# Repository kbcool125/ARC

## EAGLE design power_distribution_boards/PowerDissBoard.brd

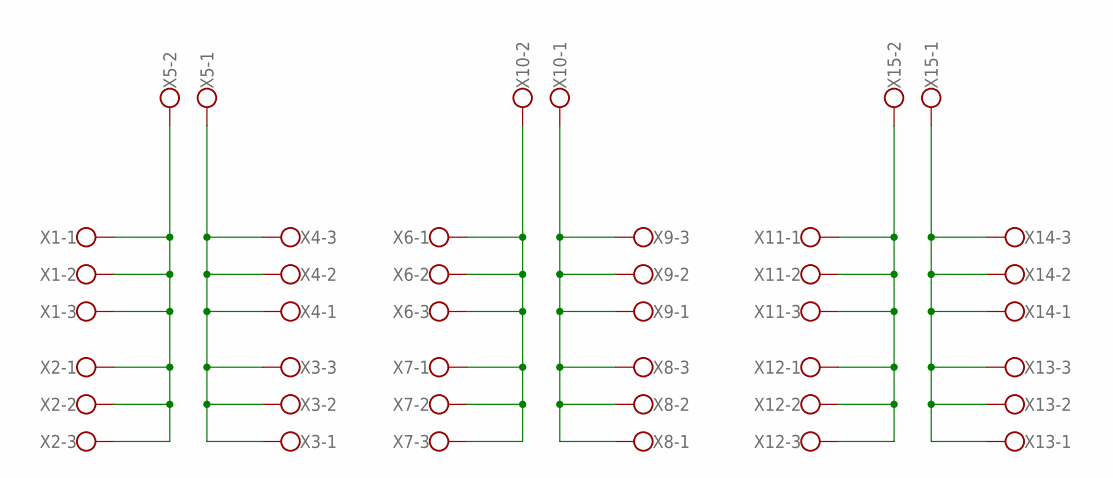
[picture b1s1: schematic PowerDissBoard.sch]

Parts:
X1, X2, X3, X4, X6, X7, X8, X9, X11, X12, X13, X14: W237-103
X5, X10, X15: W237-102

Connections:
unnamed: X1.1, X1.2, X1.3, X2.1, X2.2, X2.3, X5.2
unnamed: X3.1, X3.2, X3.3, X4.1, X4.2, X4.3, X5.1
unnamed: X6.1, X6.2, X6.3, X7.1, X7.2, X7.3, X10.2
unnamed: X8.1, X8.2, X8.3, X9.1, X9.2, X9.3, X10.1
unnamed: X11.1, X11.2, X11.3, X12.1, X12.2, X12.3, X15.2
unnamed: X13.1, X13.2, X13.3, X14.1, X14.2, X14.3, X15.1

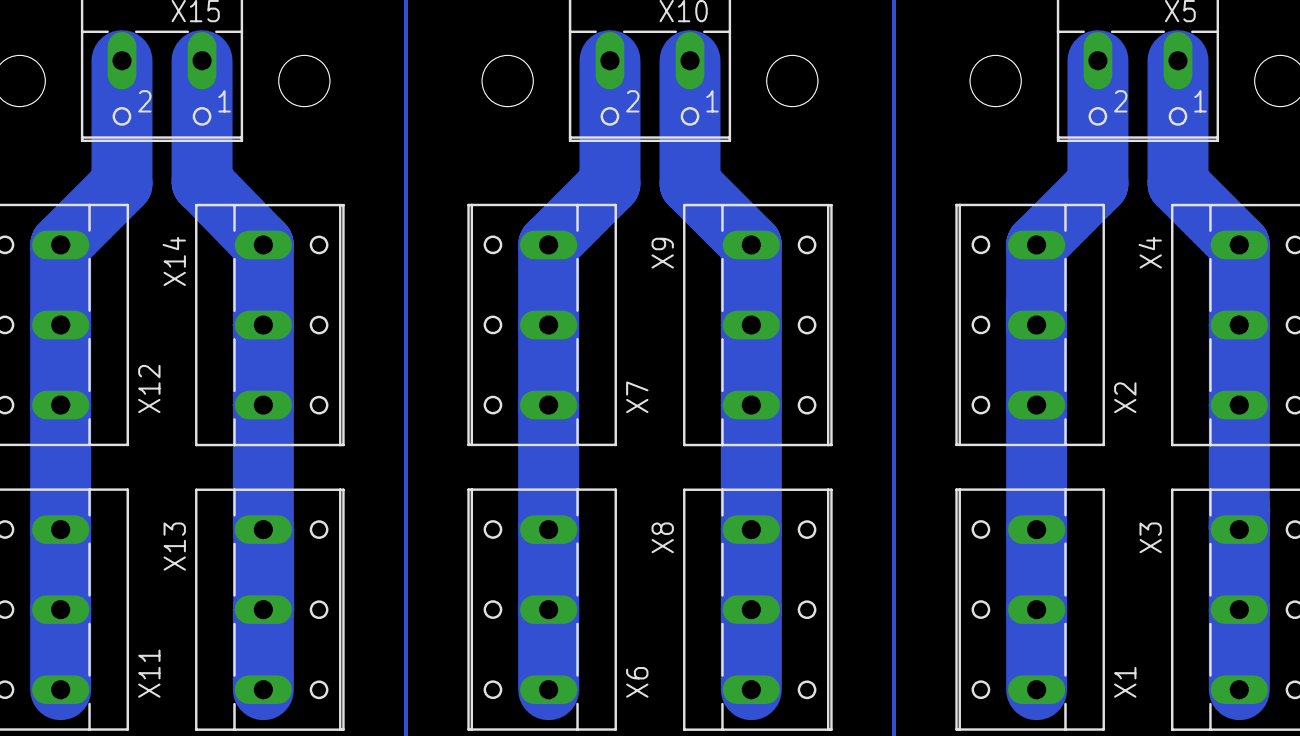
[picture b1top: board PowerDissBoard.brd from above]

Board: 2 copper layers, 15 parts (0 on the bottom side), 6 nets.

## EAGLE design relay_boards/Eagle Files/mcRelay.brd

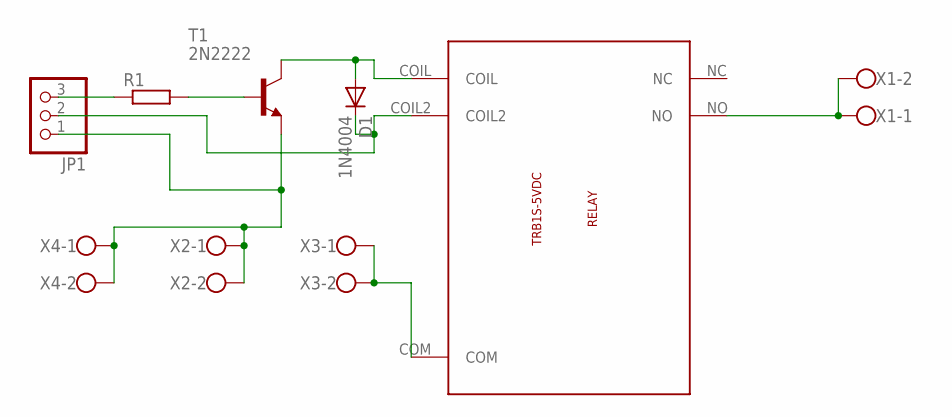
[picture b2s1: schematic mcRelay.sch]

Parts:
D1: 1N4004; DO41-10
JP1: PINHD-1X3; 1X03
R1: R-EU_0204/7; 0204/7
T1: 2N2222; TO18
U$1: TRB1S-5VDC-RELAY-DEV; TRB1S-5VDC-RELAY-PAC
X1, X2, X3, X4: W237-102

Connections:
unnamed: U$1.COM, X3.1, X3.2
unnamed: JP1.1, T1.1 (E), X2.1, X2.2, X4.1, X4.2
unnamed: U$1.NO, X1.1, X1.2
unnamed: JP1.3, R1.1
unnamed: R1.2, T1.2 (B)
unnamed: D1.A, T1.3 (C), U$1.COIL
unnamed: D1.C, JP1.2, U$1.COIL2

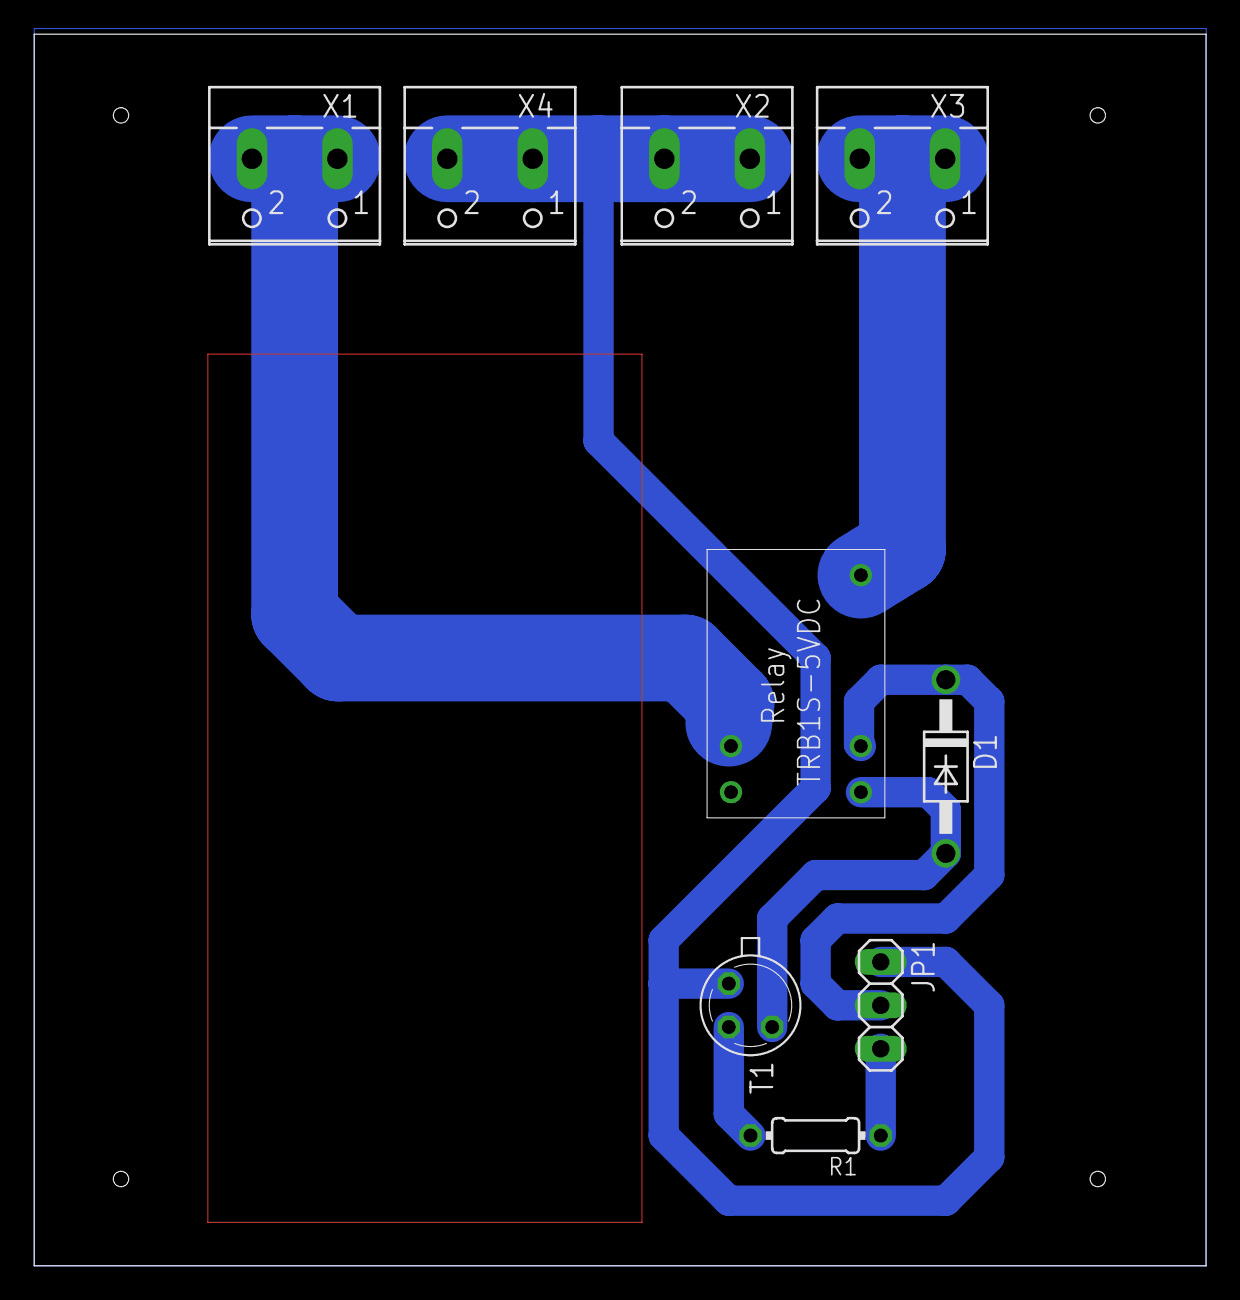
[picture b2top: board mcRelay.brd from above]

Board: 2 copper layers, 68.6 x 72.1 mm, 9 parts (0 on the bottom side), 7 nets.

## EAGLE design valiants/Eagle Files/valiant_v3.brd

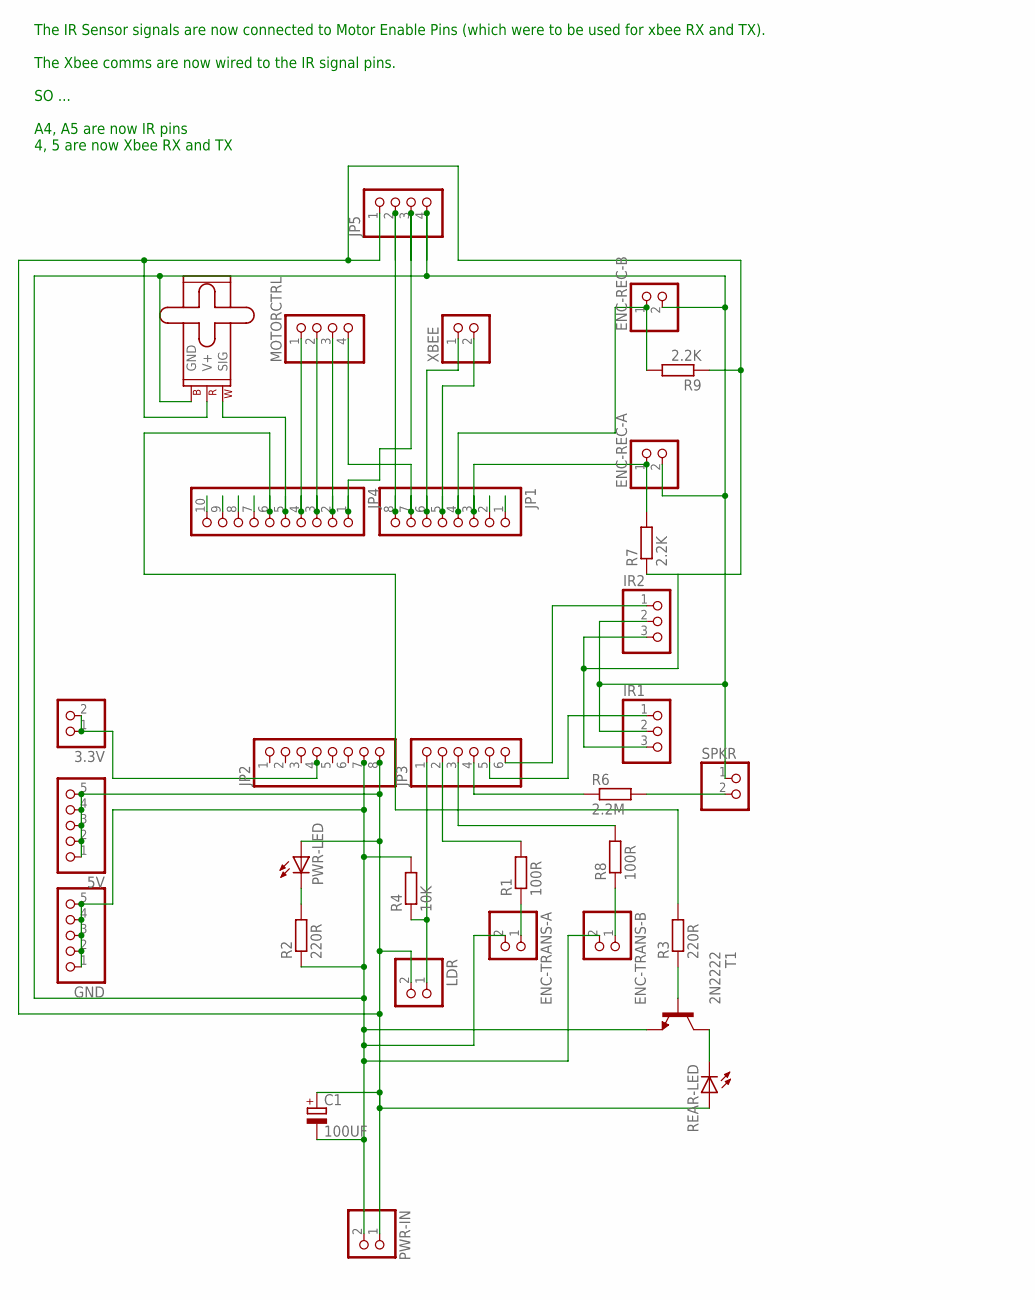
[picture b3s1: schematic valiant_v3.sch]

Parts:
3.3V: PINHD-1X2; 1X02
5V: PINHD-1X5; 1X05
C1: 100UF; E2,5-6E
ENC-REC-A: PINHD-1X2; 1X02
ENC-REC-B: PINHD-1X2; 1X02
ENC-TRANS-A: PINHD-1X2; 1X02
ENC-TRANS-B: PINHD-1X2; 1X02
GND: PINHD-1X5; 1X05
IR1, IR2: PINHD-1X3; 1X03
JP1, JP2: PINHD-1X8; 1X08
JP3: PINHD-1X6; 1X06
JP4: PINHD-1X10; 1X10
JP5: PINHD-1X4; 1X04
LDR: PINHD-1X2; 1X02
M1: SMALL_SERVO; 1X03
MOTORCTRL: PINHD-1X4; 1X04
PWR-IN: PINHD-1X2; 1X02
PWR-LED: LED5MM
R1, R8: 100R; 0204/7
R2, R3: 220R; 0204/7
R4: 10K; 0204/7
R6: 2.2M; 0204/7
R7, R9: 2.2K; 0204/7
REAR-LED: LED5MM
SPKR: PINHD-1X2; 1X02
T1: 2N2222; TO92-EBC-OVAL
XBEE: PINHD-1X2; 1X02

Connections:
unnamed: R3.1, T1.B
unnamed: JP1.8, JP5.2
unnamed: JP1.7, MOTORCTRL.4
unnamed: JP4.2, MOTORCTRL.3
unnamed: JP4.3, MOTORCTRL.2
unnamed: JP4.4, MOTORCTRL.1
unnamed: JP4.1, JP5.3
unnamed: ENC-TRANS-A.1, R1.1
unnamed: JP3.1, LDR.1, R4.1
unnamed: JP3.2, R1.2
unnamed: JP3.3, R8.2
unnamed: JP4.6, R3.2
unnamed: ENC-REC-A.1, JP1.3, R7.2
unnamed: 3.3V.1, 3.3V.2, JP2.4
unnamed: 5V.1, 5V.2, 5V.3, 5V.4, 5V.5, C1.+, IR1.3, IR2.3, JP2.8, JP5.1, LDR.2, M1.2 (V+), PWR-IN.1, PWR-LED.A, R7.1, R9.1, REAR-LED.A
unnamed: ENC-TRANS-B.1, R8.1
unnamed: PWR-LED.K (C), R2.2
unnamed: JP4.5, M1.1 (SIG)
unnamed: REAR-LED.K (C), T1.C
unnamed: IR1.1, JP3.5
unnamed: JP1.6, XBEE.1
unnamed: JP1.5, XBEE.2
unnamed: ENC-REC-B.1, JP1.4, R9.2
unnamed: R6.2, SPKR.2
unnamed: JP3.4, R6.1
unnamed: C1.-, ENC-REC-A.2, ENC-REC-B.2, ENC-TRANS-A.2, ENC-TRANS-B.2, GND.1, GND.2, GND.3, GND.4, GND.5, IR1.2, IR2.2, JP2.7, JP5.4, M1.3 (GND), PWR-IN.2, R2.1, R4.2, SPKR.1, T1.E
unnamed: IR2.1, JP3.6

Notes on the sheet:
The IR Sensor signals are now connected to Motor Enable Pins (which were to be used for xbee RX and TX). The Xbee comms are now wired to the IR signal pins. SO ... A4, A5 are now IR pins 4, 5 are now Xbee RX and TX

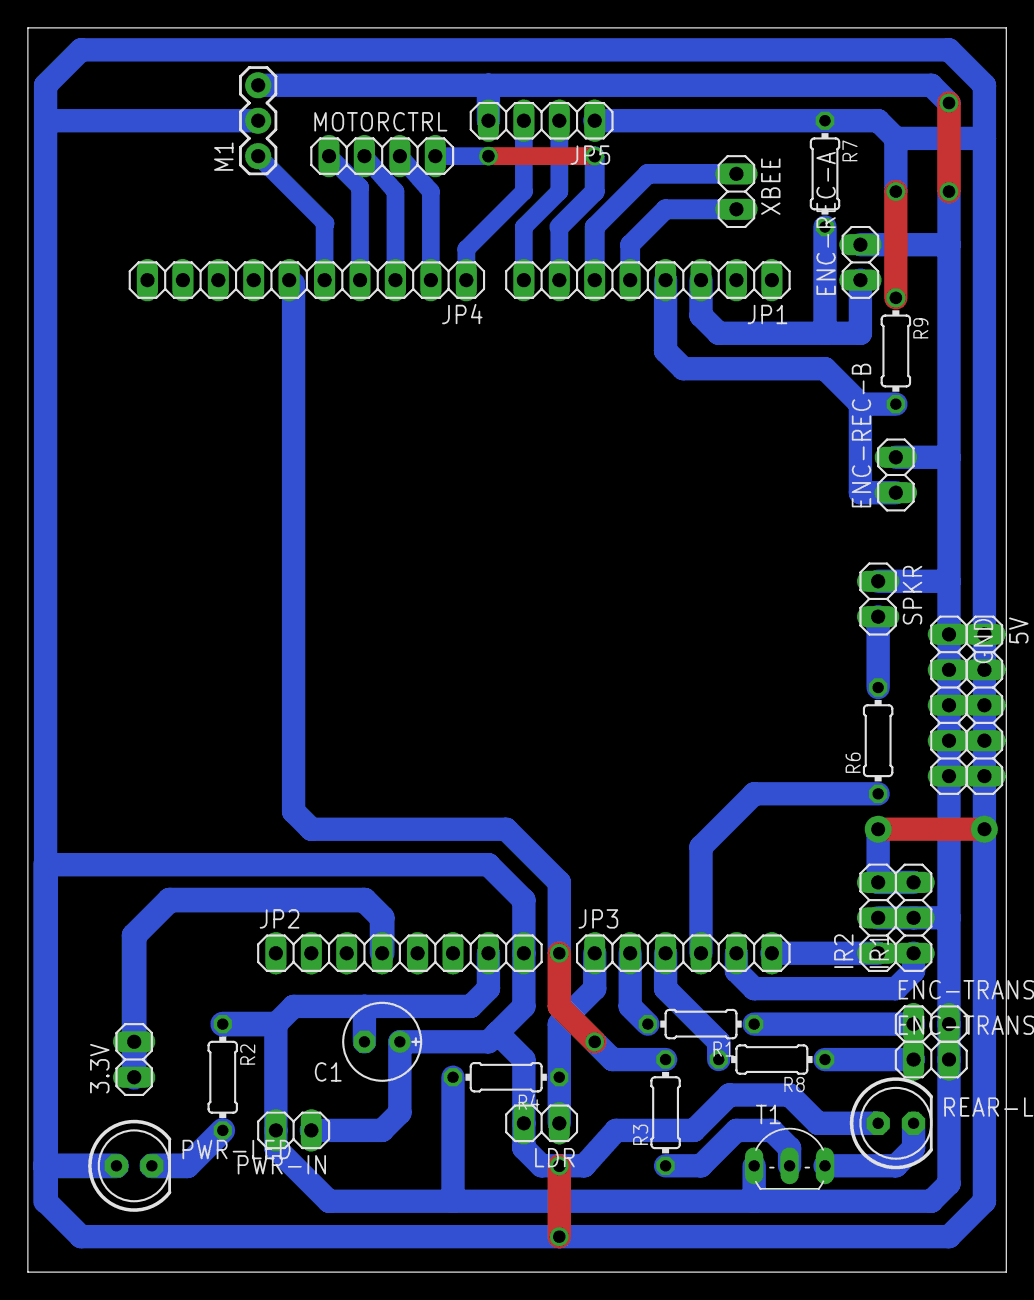
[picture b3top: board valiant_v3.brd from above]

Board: 2 copper layers, 70.1 x 89.2 mm, 32 parts (0 on the bottom side), 27 nets.

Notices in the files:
parts and their libraries:
SparkFun-Electromechanical: Licensing: Creative Commons ShareAlike 4.0 International - https://creativecommons.org/licenses/by-sa/4.0
